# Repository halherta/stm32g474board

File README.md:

# EmbLynx

An embedded systems development board based on the **STM32G474RE** microcontroller.

EmbLynx is a compact, feature-rich development board built around ST's STM32G474RE — a mixed-signal Cortex-M4 SoC with an unusually dense analog front end (5x ADC, 7x DAC, 6x OPAMP, 7x comparator) alongside DSP/math accelerators aimed at digital power conversion, motor control, and precision sensing. The board exposes that analog and digital peripheral set on standard 0.1" headers so it can be used as a general-purpose prototyping platform or stacked with daughterboards.

Full write-up: [hussamtalkstech.com/emblynx](https://hussamtalkstech.com/emblynx/)

## Features

- **MCU:** STM32G474RE (Arm Cortex-M4F, up to 170 MHz, 512 KB Flash, 128 KB SRAM)
- **Power input:**
  - Reverse-polarity-protected DC jack or Vin pin (6–30 V), stepped down via an AP63205WU buck converter to 5 V
  - Direct 5 V input via I/O header pins or USB-C (with TVS protection and 22 Ω series resistors)
  - 3.3 V rail generated from the 5 V rail via an LDO
- **Debug:** STDC14 SWD/JTAG/serial port (STLink-V3 compatible)
- **User I/O:** RESET and BOOT0 buttons (USB DFU-friendly), user pushbutton (PC13), power LED, user LED (PD2)
- **Analog support:** Jumper-selectable Vref (+3V3 or external), filtering on VDD_A / VREF+
- **Current measurement:** IDD jumper (JP2) isolates the microcontroller's own 3.3 V rail (+3V3) from the peripheral/LED rail (+3V30) for clean current measurements
- **RTC backup:** BAT54C dual-Schottky arrangement feeds VBAT from either a coin-cell on the I/O header or +3V3 when no battery is present
- **Form factor:** 2.2" x 3.3", 4-layer PCB, 6x 8-pin 0.1" I/O headers (stacking-header compatible)

## STM32G474RE peripheral highlights

| Category | Details |
|---|---|
| Core | Cortex-M4F w/ FPU + DSP, 170 MHz, ART Accelerator, 0-wait-state Flash |
| Memory | 512 KB dual-bank Flash (ECC), 128 KB SRAM (parity on select blocks), 32 KB CCM-SRAM |
| Math accelerators | CORDIC (trig/hyperbolic), FMAC (FIR/IIR/3p3z filters) |
| Timers | 17 total, incl. HRTIM (184 ps resolution), motor-control timers, watchdogs |
| Connectivity | 3x FDCAN, 4x I2C (Fast-mode+), 5x USART/UART, 1x LPUART, 4x SPI/2x I2S, SAI, USB 2.0 FS, USB-C/UCPD |
| ADC | 5x independent 12-bit SAR, up to 4 Msps each (8 Msps interleaved), up to 16-bit via oversampling |
| DAC | 7 channels (3 buffered external @ 1 Msps, 4 unbuffered internal @ 15 Msps) |
| OPAMP | 6x, externally accessible, configurable as PGAs (x2–x64), ~13 MHz bandwidth |
| Comparator | 7x, 16.7 ns propagation delay, programmable hysteresis |
| Reference | VREFBUF with 2.048 V / 2.5 V / 2.95 V presets |
| Other | 16-channel DMA, FSMC/Quad-SPI, hardware RNG, CRC, internal temp sensor |

## Getting started

### Prerequisites

- [KiCad](https://www.kicad.org/) 7.x or later

### Opening the project

1. Clone this repository:
   ```bash
   git clone https://github.com/halherta/stm32g474board.git
   ```
2. Open `stm32g474board.kicad_pro` in KiCad.

### Schematic

A rendered PDF of the full schematic is included [here](https://github.com/halherta/stm32g474board/blob/main/stm32g474board.pdf).

### Layout

### Parts Library

my latest Kicad footprint / symbol parts library cab always be found [here](https://github.com/halherta/mykicadlibrary)

## Power architecture

| Rail | Source | Notes |
|---|---|---|
| VIN (6–30 V) | DC jack or I/O header | Reverse-polarity protected |
| +5V | VIN → AP63205WU buck, or direct 5 V pin, or USB-C | USB-C input has TVS + 22 Ω series protection |
| +3V30 | +5V → LDO | Powers LEDs, pull-ups, always-on peripherals |
| +3V3 | +3V30 → IDD jumper (JP2) | Powers the MCU only; JP2 allows current measurement of the MCU in isolation |
| VBAT | Coin cell (I/O header) or +3V3 | Selected via BAT54C dual-Schottky diodes |

## Credits

Designed by [Hussam](https://hussamtalkstech.com/about) — [hussamtalkstech.com](https://hussamtalkstech.com/)

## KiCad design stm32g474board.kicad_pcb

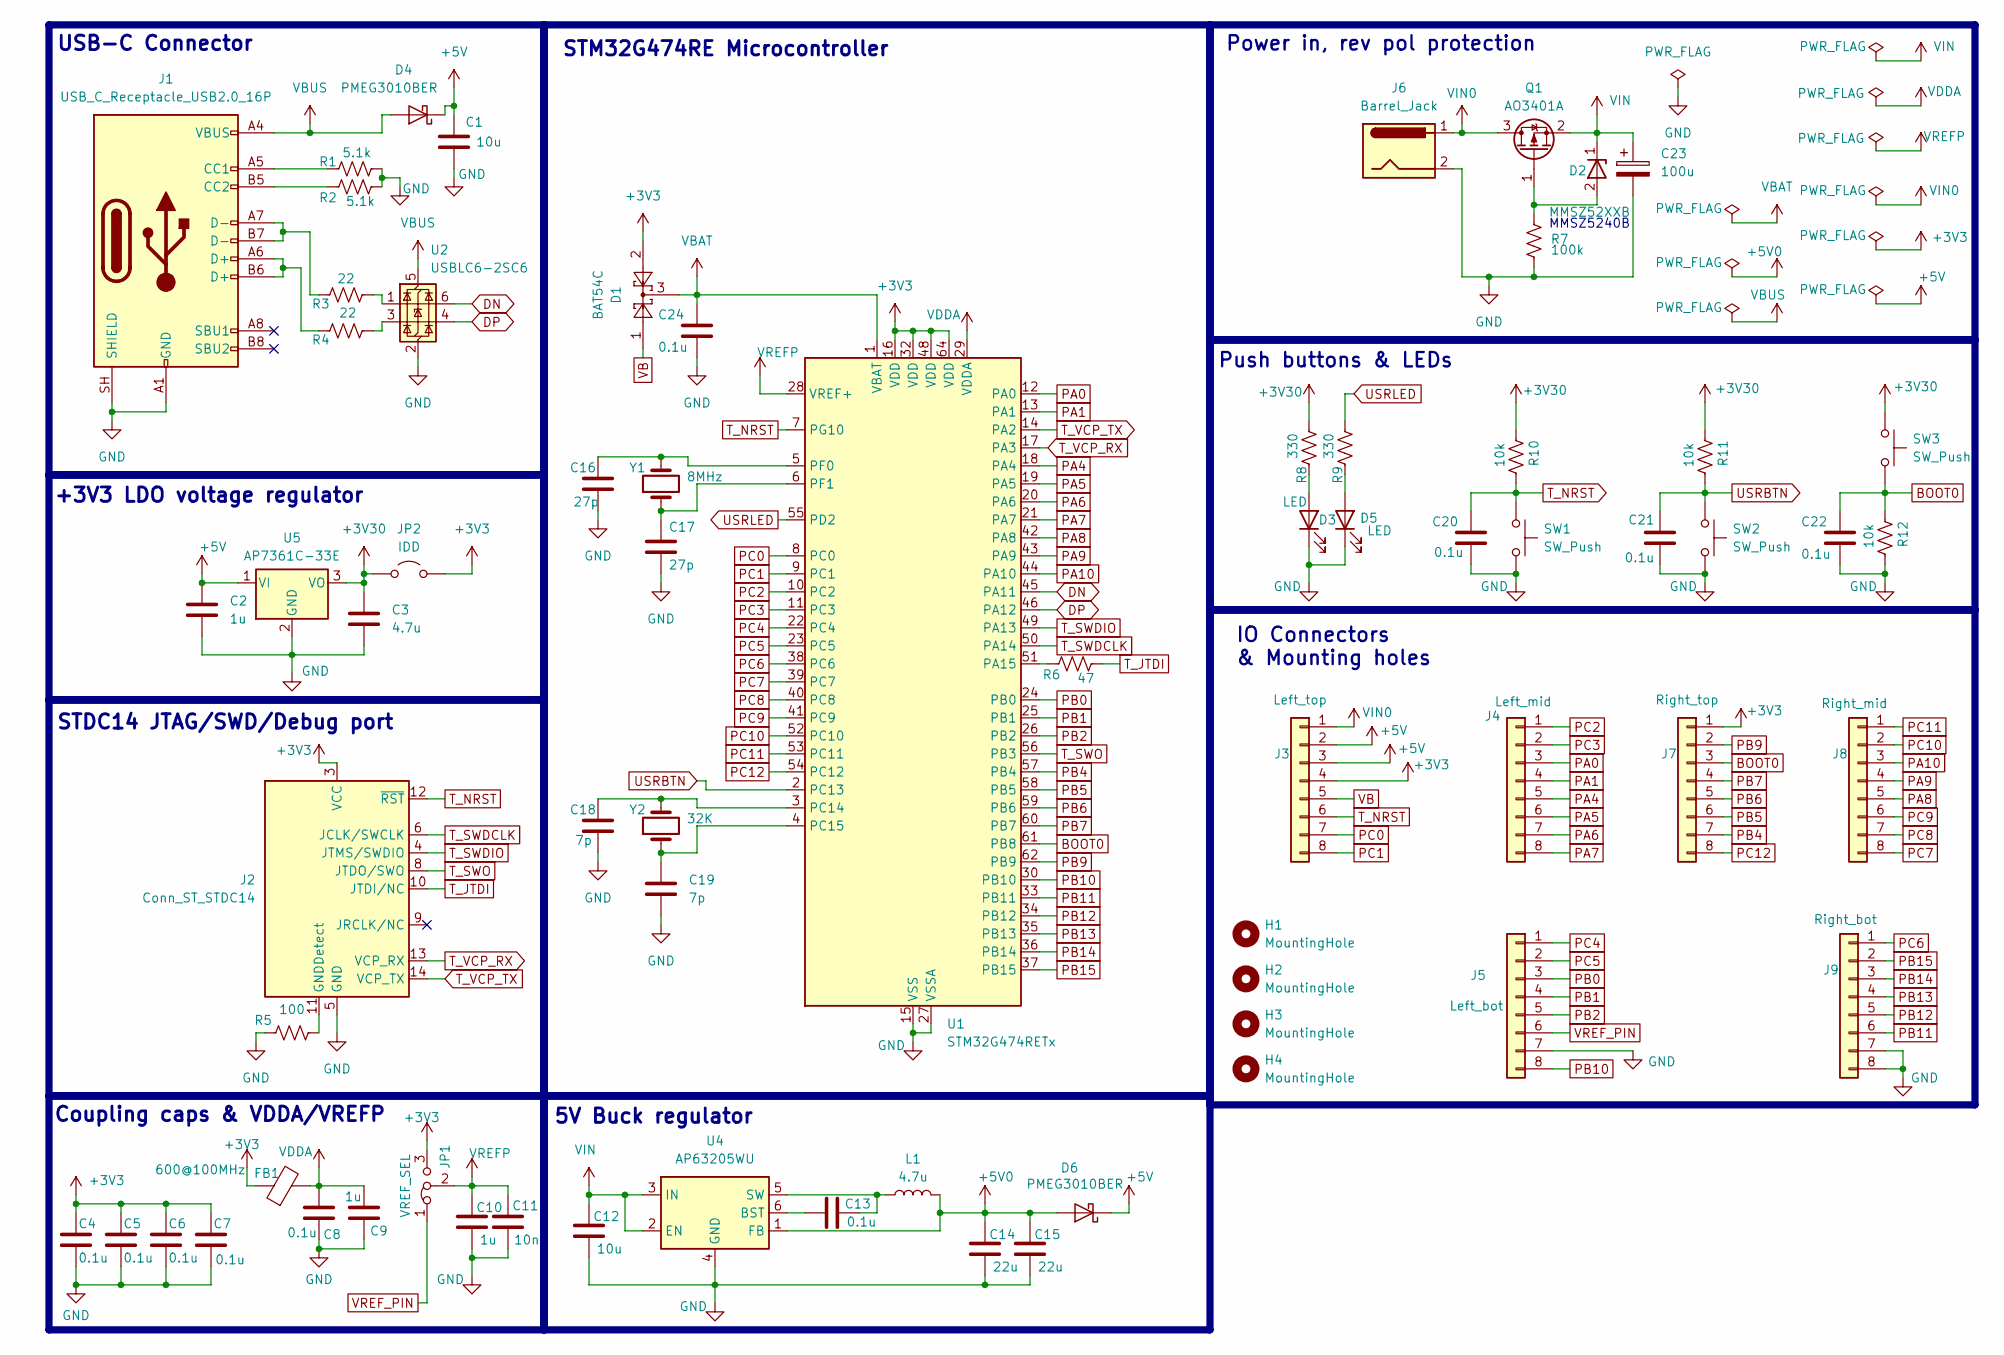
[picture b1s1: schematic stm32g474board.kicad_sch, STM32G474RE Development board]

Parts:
C1, C12: 10u; C_0805_2012Metric_Pad1.18x1.45mm_HandSolder
C2, C9, C10: 1u; C_0805_2012Metric_Pad1.18x1.45mm_HandSolder
C3: 4.7u; C_0805_2012Metric_Pad1.18x1.45mm_HandSolder
C4, C5, C6, C7, C8, C13, C20, C21, C22, C24: 0.1u; C_0805_2012Metric_Pad1.18x1.45mm_HandSolder
C11: 10n; C_0805_2012Metric_Pad1.18x1.45mm_HandSolder
C14, C15: 22u; C_0805_2012Metric_Pad1.18x1.45mm_HandSolder
C16, C17: 27p; C_0805_2012Metric_Pad1.18x1.45mm_HandSolder
C18, C19: 7p; C_0805_2012Metric_Pad1.18x1.45mm_HandSolder
C23: 100u; CP_Elec_6.3x7.7
D1: BAT54C; SOT-23
D2: MMSZ52XXB; D_SOD-123
D3, D5: LED; LED_0805_2012Metric_Pad1.15x1.40mm_HandSolder
D4, D6: PMEG3010BER; Nexperia_CFP3_SOD-123W
FB1: 600@100MHz; L_0603_1608Metric
H1, H2, H3, H4: MountingHole; MountingHole_3.2mm_M3
J1: USB_C_Receptacle_USB2.0_16P; USB_C_Receptacle_GCT_USB4110
J2: Conn_ST_STDC14; PinHeader_2x07_P1.27mm_Vertical_SMD
J3: Left_top; PinSocket_1x08_P2.54mm_Vertical
J4: Left_mid; PinSocket_1x08_P2.54mm_Vertical
J5: Left_bot; PinSocket_1x08_P2.54mm_Vertical
J6: Barrel_Jack; CUI_PJ-037AH
J7: Right_top; PinSocket_1x08_P2.54mm_Vertical
J8: Right_mid; PinSocket_1x08_P2.54mm_Vertical
J9: Right_bot; PinSocket_1x08_P2.54mm_Vertical
JP1: VREF_SEL; PinHeader_1x03_P2.54mm_Vertical
JP2: IDD; PinHeader_1x02_P2.54mm_Vertical
L1: 4.7u; L_Coilcraft_XxL4040
Q1: AO3401A; SOT-23
R1, R2: 5.1k; R_0805_2012Metric_Pad1.20x1.40mm_HandSolder
R3, R4: 22; R_0805_2012Metric_Pad1.20x1.40mm_HandSolder
R5: 100; R_0805_2012Metric_Pad1.20x1.40mm_HandSolder
R6: 47; R_0805_2012Metric_Pad1.20x1.40mm_HandSolder
R7: 100k; R_0805_2012Metric_Pad1.20x1.40mm_HandSolder
R8, R9: 330; R_0805_2012Metric_Pad1.20x1.40mm_HandSolder
R10, R11, R12: 10k; R_0805_2012Metric_Pad1.20x1.40mm_HandSolder
SW1, SW2, SW3: SW_Push; SW_SPST_PTS645Sx43SMTR92
U1: STM32G474RETx; LQFP-64_10x10mm_P0.5mm
U2: USBLC6-2SC6; SOT-23-6
U4: AP63205WU; TSOT-23-6_HandSoldering
U5: AP7361C-33E; SOT-223-3_TabPin2
Y1: 8MHz; Crystal_SMD_5032-2Pin_5.0x3.2mm
Y2: 32K; Crystal_SMD_3215-2Pin_3.2x1.5mm

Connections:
+3V3: C4.1, C5.1, C6.1, C7.1, D1.2, FB1.1, J2.3 (VCC), J3.4, J7.1, JP1.3 (B), JP2.2 (B), U1.16 (VDD), U1.32 (VDD), U1.48 (VDD), U1.64 (VDD)
+3V30: C3.1, JP2.1 (A), R8.2, R10.2, R11.2, SW3.1, U5.3 (VO)
+5V: C1.1, C2.1, D4.1 (K), D6.1 (K), J3.2, J3.3, U5.1 (VI)
+5V0: C14.1, C15.1, D6.2 (A), L1.2, U4.1 (FB)
BOOT0: C22.1, J7.3, R12.2, SW3.2, U1.61 (PB8)
DN: U1.45 (PA11), U2.6 (I/O1)
DP: U1.46 (PA12), U2.4 (I/O2)
GND: C1.2, C2.2, C3.2, C4.2, C5.2, C6.2, C7.2, C8.2, C9.2, C10.2, C11.2, C12.2, C14.2, C15.2, C16.2, C17.2, C18.2, C19.2, C20.2, C21.2, C22.2, C23.2, C24.2, D3.1 (K), D5.1 (K), J1.A1 (GND), J1.A12 (GND), J1.B1 (GND), J1.B12 (GND), J1.SH (SHIELD), J2.5 (GND), J2.7 (GND), J5.7, J6.2, J9.7, J9.8, R1.2, R2.2, R5.1, R7.2, R12.1, SW1.2, SW2.2, U1.15 (VSS), U1.27 (VSSA), U1.31 (VSS), U1.47 (VSS), U1.63 (VSS), U2.2 (GND), U4.4 (GND), U5.2 (GND)
unnamed: D2.2 (A), Q1.1 (G), R7.1
unnamed: D3.2 (A), R8.1
unnamed: D5.2 (A), R9.1
unnamed: J1.A5 (CC1), R1.1
unnamed: J1.B5 (CC2), R2.1
unnamed: J1.A6 (D+), J1.B6 (D+), R4.1
unnamed: J1.A7 (D-), J1.B7 (D-), R3.1
unnamed: J2.11 (GNDDetect), R5.2
unnamed: R3.2, U2.1 (I/O1)
unnamed: R4.2, U2.3 (I/O2)
unnamed: R6.1, U1.51 (PA15)
unnamed: C18.1, U1.3 (PC14), Y2.2
unnamed: C19.1, U1.4 (PC15), Y2.1
unnamed: C16.1, U1.5 (PF0), Y1.2
unnamed: C17.1, U1.6 (PF1), Y1.1
unnamed: C13.1, U4.6 (BST)
unnamed: C13.2, L1.1, U4.5 (SW)
PA0: J4.3, U1.12 (PA0)
PA1: J4.4, U1.13 (PA1)
PA4: J4.5, U1.18 (PA4)
PA5: J4.6, U1.19 (PA5)
PA6: J4.7, U1.20 (PA6)
PA7: J4.8, U1.21 (PA7)
PA8: J8.5, U1.42 (PA8)
PA9: J8.4, U1.43 (PA9)
PA10: J8.3, U1.44 (PA10)
PB0: J5.3, U1.24 (PB0)
PB1: J5.4, U1.25 (PB1)
PB2: J5.5, U1.26 (PB2)
PB4: J7.7, U1.57 (PB4)
PB5: J7.6, U1.58 (PB5)
PB6: J7.5, U1.59 (PB6)
PB7: J7.4, U1.60 (PB7)
PB9: J7.2, U1.62 (PB9)
PB10: J5.8, U1.30 (PB10)
PB11: J9.6, U1.33 (PB11)
PB12: J9.5, U1.34 (PB12)
PB13: J9.4, U1.35 (PB13)
PB14: J9.3, U1.36 (PB14)
PB15: J9.2, U1.37 (PB15)
PC0: J3.7, U1.8 (PC0)
PC1: J3.8, U1.9 (PC1)
PC2: J4.1, U1.10 (PC2)
PC3: J4.2, U1.11 (PC3)
PC4: J5.1, U1.22 (PC4)
PC5: J5.2, U1.23 (PC5)
PC6: J9.1, U1.38 (PC6)
PC7: J8.8, U1.39 (PC7)
PC8: J8.7, U1.40 (PC8)
PC9: J8.6, U1.41 (PC9)
PC10: J8.2, U1.52 (PC10)
PC11: J8.1, U1.53 (PC11)
PC12: J7.8, U1.54 (PC12)
T_JTDI: J2.10 (JTDI/NC), R6.2
T_NRST: C20.1, J2.12 (~RST), J3.6, R10.1, SW1.1, U1.7 (PG10)
T_SWDCLK: J2.6 (JCLK/SWCLK), U1.50 (PA14)
T_SWDIO: J2.4 (JTMS/SWDIO), U1.49 (PA13)
T_SWO: J2.8 (JTDO/SWO), U1.56 (PB3)
T_VCP_RX: J2.13 (VCP_RX), U1.17 (PA3)
T_VCP_TX: J2.14 (VCP_TX), U1.14 (PA2)
USRBTN: C21.1, R11.1, SW2.1, U1.2 (PC13)
USRLED: R9.2, U1.55 (PD2)
VB: D1.1, J3.5
VBAT: C24.1, D1.3, U1.1 (VBAT)
VBUS: D4.2 (A), J1.A4 (VBUS), J1.A9 (VBUS), J1.B4 (VBUS), J1.B9 (VBUS), U2.5 (VBUS)
VDDA: C8.1, C9.1, FB1.2, U1.29 (VDDA)
VIN: C12.1, C23.1, D2.1 (K), Q1.2 (S), U4.2 (EN), U4.3 (IN)
VIN0: J3.1, J6.1, Q1.3 (D)
VREFP: C10.1, C11.1, JP1.2 (C), U1.28 (VREF+)
VREF_PIN: J5.6, JP1.1 (A)

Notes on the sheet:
Coupling caps & VDDA/VREFP
STM32G474RE Microcontroller
5V Buck regulator
Push buttons & LEDs
USB-C Connector
IO Connectors & Mounting holes
MMSZ5240B
+3V3 LDO voltage regulator
Power in, rev pol protection
STDC14 JTAG/SWD/Debug port

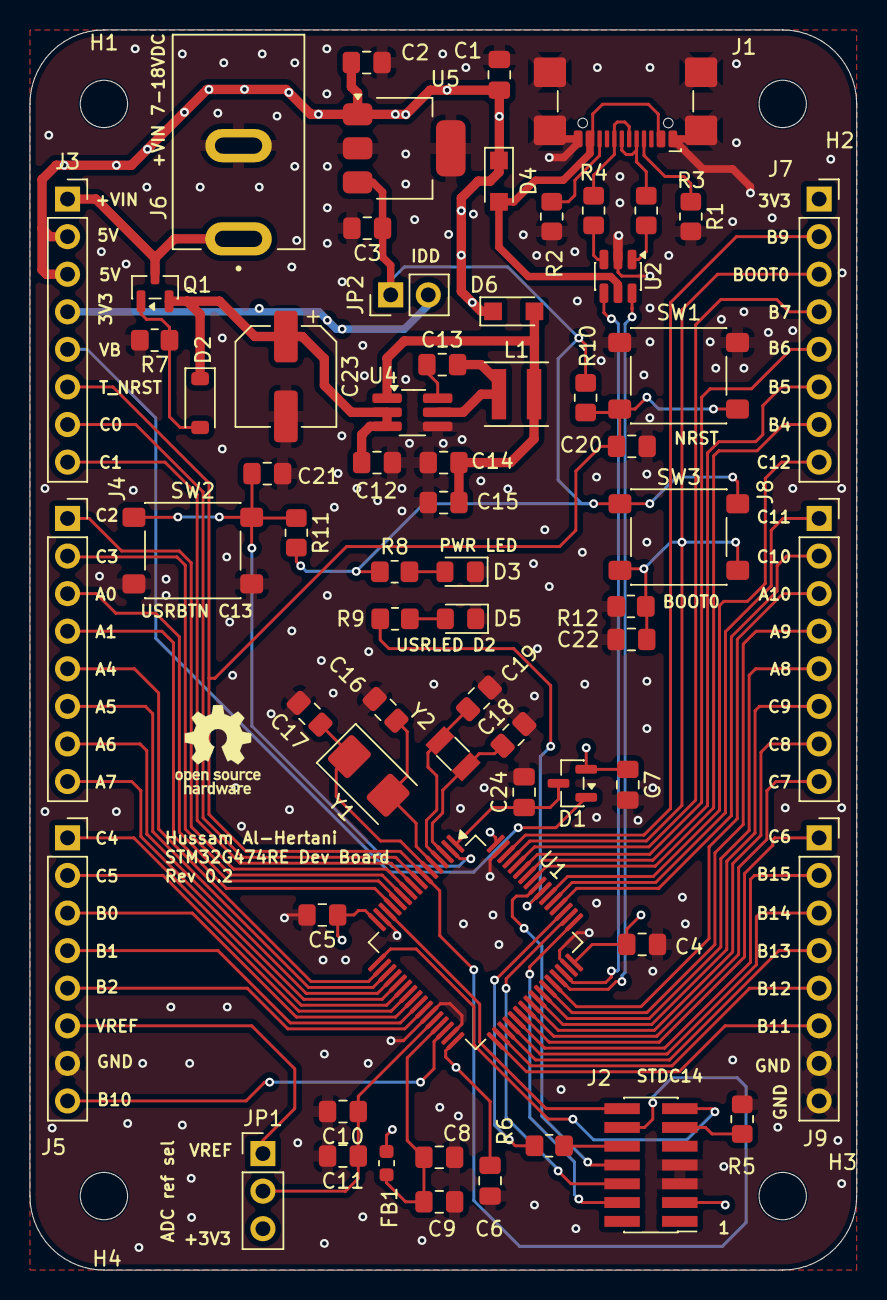
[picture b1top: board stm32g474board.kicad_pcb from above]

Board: 4 copper layers, 55.9 x 83.8 mm, 69 parts (0 on the bottom side), 78 nets.
